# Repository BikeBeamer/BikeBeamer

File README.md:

# BikeBeamer

## Overview

This is my next generation of bike POV displays based on [bkpvdsply](https://github.com/locxter/bkpvdsply). With much extended functionality, a more polished design and an easier user-experience, the goal for it is to extend my capabilities and experiment with building a "real product" that lives up to the expectations one might have. Also take a look at the [project website](https://bikebeamer.com) or the launch video:

## Dependencies

I generally try to minimize dependencies, but I'm a one man crew and can therefore only support Debian-based Linux distributions as I'm running one myself. Anyway, you need to have the following packages installed for everything to work properly:

- Arduino IDE as a way to compile the Arduino code. Install it with `sudo apt install arduino`.
- MPU6050_tockn library for communicating with the gyroscope. Install it via the integrated library manager.
- Adafruit NeoPixel library for controlling the LEDs. Install it via the integrated library manager.

Note there is an [issue with the ESP32 core library >=3.x and the NeoPixel library when using more than 75 pixels](https://github.com/adafruit/Adafruit_NeoPixel/issues/402). There is a [forked library with a fix](https://github.com/teknynja/Adafruit_NeoPixel/tree/esp32_rmt_memory_allocation_fix_safe).

There some slight differences, depending on which major version of the Arduino IDE you are using. Extensions are not compatible with both versions. An extension is needed for uploading the data to the ESP32 LittleFS.

### Arduino IDE 1.x

Use the Arduino ESP32 LittleFS uploader for uploading the data. Install it via the [installation guide](https://github.com/lorol/arduino-esp32fs-plugin).

### Arduino IDE 2.x

Use the [Arduino LittleFS upload extension](https://github.com/earlephilhower/arduino-littlefs-upload).

## Improvements over bkpvdsply

### Hardware

- [x] Reduce the overall height to fit slimmer wheels
- [x] Rethink the mounting system to be easier for the user
- [x] FAILED: ~~Switch to a reusable cable tie alternative~~
- [x] Improve the water resistance (ideally water proof)
- [x] Make everything more balanced (equal weight distribution)
- [x] Add LED strips to both sides

### Electronics

- [x] Improve battery runtime
- [x] ABANDONED VIA SWITCH TO BATTERIES: ~~Make charging easier~~
- [x] Develop a properly sized power supply unit
- [x] Use custom-made circuit boards
- [ ] Switch to all SMT components
- [ ] Off-hand to production to a specialized vendor

### Software

- [x] Implement customizable LED strip positions (relative to control board)
- [x] Allow the rotation direction to be reversed (when the control board back faces right)
- [x] Use LED trips on both sides to display the image
- [x] Allow the image to be mirrored for the second side (useful for symbols and graphics, but not text)
- [ ] Reduce storage size of images (ideally via file compression)
- [ ] Add the ability to make animations with more than 2 images
- [x] Improve image stability (more exact rotation and speed change detection, smooth measuremets)
- [x] Implement customizable sampling threshold (allowed variation to trigger rotation detection)
- [X] Rework API with clearer endpoints
- [x] Load existing settings to UI for easier incremental changes
- [x] Store and load associative names of images for easier identification

And more to come...

## How to build it

In order to create a device able to produce such wonderful visuals, you only need rather common components (an ESP32, some LED strips, an IMU and some sort of power supply), but their combination results in this really special outcome. Everything is based on a custom PCB onto which all of the other components are soldered and which is then encased in 3D printed parts. Here's what the finished outcome should look like:

Even though many sequences of assembly will result in functional boards, here's how I assemble them after trying out several approaches with varying success:

1. In case you went for the cheap battery holders from Amazon, cut off the brim on the bottom, sand this side for better adhesive contact, shorten the wires and tin them in advance.
2. As always, parts should be soldered in the order of their height. So start off with cutting the LED strips to their desired length of 32 LEDs and then solder them down with the arrows facing towards the slim end of the boards from each side. It's easiest to solder one side of a strip, apply some instant glue along it's way and then solder the other one mounting it into place.
3. After that's done, continue with the diodes - be careful to install them the right way around (silver ring facing the marked direction) - and On/Off switch.
4. Now it's time install the ESP32 and IMU. Solder male headers facing down to the D1 Mini board in case not already done and then mount their female counterparts to the main PCB. You can also fill the contacts on the other boards, but that's not necessary. Then add the right-angle connector to the MPU-6050 board so that it can be mounted vertically to the PCB with its back facing to the wide end of the board and solder it down.
5. You're getting there, just add the screw terminals and then capacitors with the polarity of the latter being crucial (white component markings should face the filled side on the PCB).
6. If necessary glue down the battery holders and then solder them into place - this can be quite tight, but should be doable.
7. To prevent shorts with the spokes from happing isolate the back side with some duck tape or equivalent material. If you want everything to be more moisture resistant, you can also look into spray rubber products.
8. Finally, install the connection cables in the consistent matter and make sure that there are no shorts or other critical mistakes.
9. Once the electronics are done, cut the Plexiglas sheet into 8 14x222mm big pieces, glue them into the 3D prints (4 bottom + 4 top parts) and put them together (bottom part + PCB + top part, 4 times).

Below is a full bill of materials with German sources for all required non-printable parts:

| Quantity (not necessarily the order quantity): | Item: | Source: |
| --- | --- | --- |
| 1 | ESP32 D1 Mini | [Amazon](https://www.amazon.de/dp/B08BTLYSTM) |
| 1 | MPU-6050 | [Amazon](https://www.amazon.de/AZDelivery-MPU-6050-3-Achsen-Gyroskop-Beschleunigungssensor-Arduino/dp/B07TKLYBD6) |
| 2 | LED strip (144 LEDs/m) | [Amazon](https://www.amazon.de/dp/B08JJ6S1HC) |
| 12 | Battery holder | [RS Components](https://de.rs-online.com/web/p/batteriehalter/6119576) OR [Amazon](https://www.amazon.de/AA-Batteriehalter-KUOQIY-Batteriehalter-Drahtkabeln-Schraubendreher/dp/B0C2Q6JV88) |
| 4 | Power switch | [RS Components](https://de.rs-online.com/web/p/schiebeschalter/7347334) OR [Amazon](https://www.amazon.de/RUNCCI-YUN-Schiebeschalter-Positionen-Vertikal-Schalter/dp/B09TVDZ8P2) |
| 12 | Power smoothing capacitor (1000μF) | [RS Components](https://de.rs-online.com/web/p/aluminium-elektrolytkondensatoren/1815420) OR [Amazon](https://www.amazon.de/Kondensator-radial-1000%C2%B5F-RJF-10V102MH4-1000uF/dp/B07H9BFK31) |
| 4 | Reverse-voltage diode (1N5820) | [RS Components](https://de.rs-online.com/web/p/schottky-dioden-und-gleichrichter/6547224) OR [Amazon](https://www.amazon.de/ALLECIN-1N5820-Schottky-Gleichrichterdiode-Siliziumdioden/dp/B0CKSH71TP) |
| 6 | Screw terminal | [RS Components](https://de.rs-online.com/web/p/leiterplatten-printklemmen/1731613) OR [Amazon](https://www.amazon.de/RUNCCI-St%C3%BCcke-Terminal-Schraubklemme-Steckverbinder/dp/B07RR7D267) |
| 6 | JST SM 3 pin cable | [Amazon](https://www.amazon.de/YIXISI-M%C3%A4nnlichen-Weiblichen-Steckverbinder-Elektrisch/dp/B08JV8TJ9N) |
| 12 | AA battery | [Amazon](https://www.amazon.de/Varta-Industrial-Batterie-Alkaline-Batterien-blau/dp/B00LN803LE) |
| 15 | Cable ties | [Amazon](https://www.amazon.de/Kabelbinder-Rscolila-Hochleistungs-Kabelmanagement-300mmx5mm/dp/B09MVKD5YX) |
| 1 | Duck tape | [Amazon](https://www.amazon.de/3M-Gewebeklebeband-1900-Schwarz-1-er/dp/B006MKBVNM) |
| 3 | Instant glue | [Amazon](https://www.amazon.de/Uhu-45415-Sekundenkleber-Blitzschnell-fl%C3%BCssig/dp/B001IVZMBM) |
| 1 | Plexiglas sheet | [Amazon](https://www.amazon.de/Langaelex-transparentes-Plexiglasscheibe-Ersatzglas-Projektausstellung/dp/B0CL93YGQ2) |
| 18 | Wire ferrules | [Amazon](https://www.amazon.de/BAURIX-Aderendh%C3%BClsen-Sortiment-Isolierte-sortiert/dp/B07R6N5MGC) |

## How to use it

1. Build the hardware as described above and put the batteries in.
2. Select the "WEMOS D1 MINI ESP32" board in the Arduino IDE.
3. Flash the sketch with the following settings:
    - `Upload Speed: 9215600`
    - `CPU Frequency: 240MHz (WiFi/BT)`
    - `Flash Frequency: 80MHz`
    - `Partition Scheme: No OTA (Large APP)`
    - `Core Debug Level: None`
    - `Erase All Flash Before Sketch Upload: Disabled`
4. Upload the additional files via the Arduino ESP32 LittleFS uploader.
5. After turning on BikeBeamer, give the ESP roughly half a minute to boot up.
6. Connect to the Wi-Fi network `BikeBeamer`, open any webpage (or `192.168.0.1` if the local DNS server doesn't work) and upload an image (examples are in the `images` folder).
7. Test the assembled hardware on your workbench and check if everything works as expected. Here is some reference footage:

    [Loose boards in action](loose-in-action.mp4)

    https://github.com/user-attachments/assets/22288a13-f305-4ee8-a11e-b3bcc51daa01

8. Mount it on your bike with some cable ties like this:

9. Then just hop on your bike and enjoy the glory of this next generation POV display. Here's just some inspiration:

    [Mounted boards in action](mounted-in-action.mp4)

    https://github.com/user-attachments/assets/4a3be52c-16f3-4a09-bf7f-77527c5345b7

## Developer notes

- All angles used are in counted in degrees clockwise from 12 o'clock looking at the left side of the bike
- All coordinate systems used have their origin at the bottom left
- The PCBs are mounted with the back side visible when looking at the left side of the bike and connected in clockwise direction
- All indexes in the code are zero-based, while all user interfaces and visualisations use regular one-based numbering
- All API communication is done through HTTP headers for the sake of easy parsing in the front- and backend

### Mounting visualisation

### Image display visualisation

### API

- [x] User interface: GET /index.html

#### Settings

- [x] Get stored settings: GET /api/settings
- [X] Update settings: PUT /api/settings

#### Images

- [x] Get image names: GET /api/images
- [X] Update image: PUT /api/images/{slot}

## Similiar projects

- https://subethasoftware.com/bikelights/
- https://www.kickstarter.com/projects/minimonkey/monkey-light-pro-bicycle-wheel-display-system/description
- https://learn.adafruit.com/spokepov/overview
- https://www.ladyada.net/make/spokepov/
- https://learn.adafruit.com/bike-wheel-pov-display/overview
- https://bicycletouringpro.com/hokey-spokes-bicycle-lights-review/

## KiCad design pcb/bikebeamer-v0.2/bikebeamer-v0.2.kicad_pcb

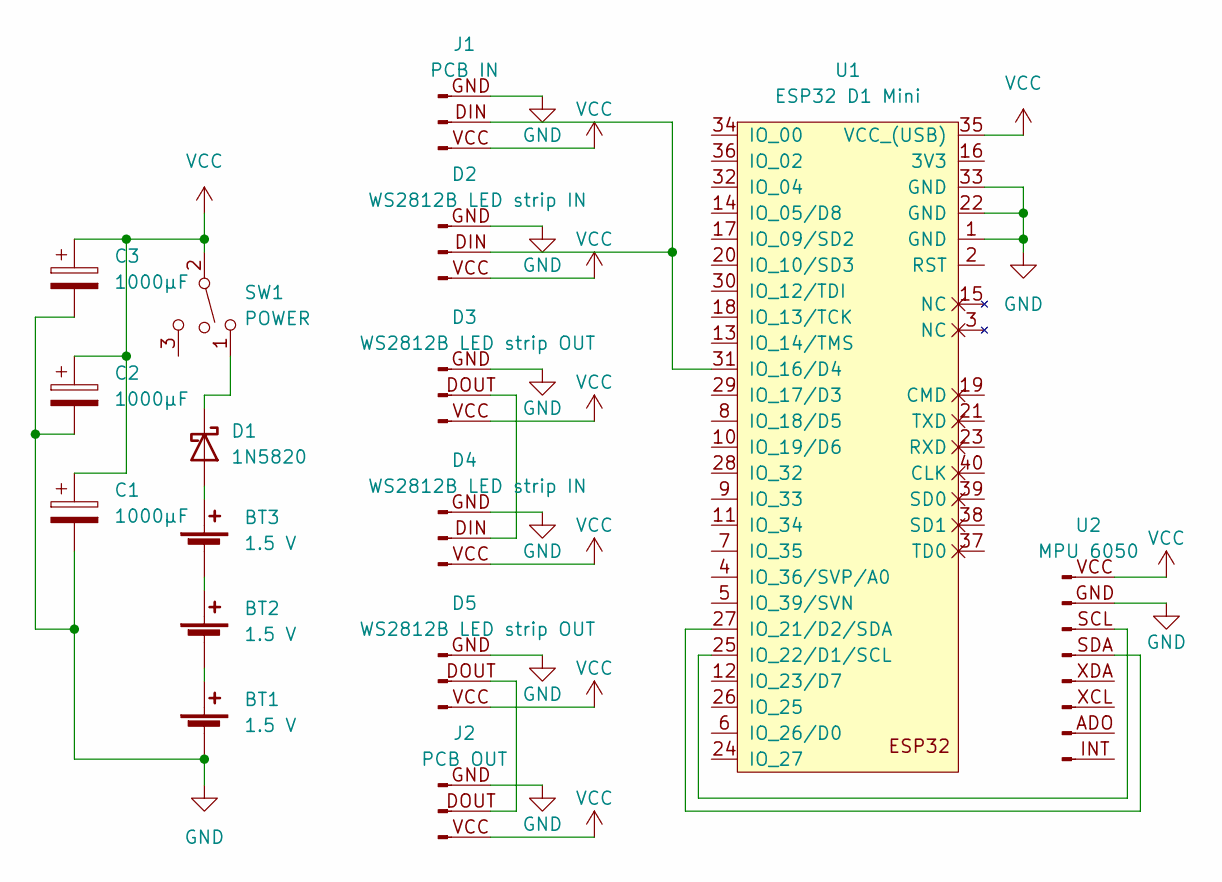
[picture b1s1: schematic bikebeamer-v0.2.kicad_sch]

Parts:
BT1, BT2, BT3: 1.5 V; BatteryHolder_Keystone_2460_1xAA
C1, C2, C3: 1000µF; CP_Radial_D10.0mm_P5.00mm
D1: 1N5820; D_DO-201AD_P15.24mm_Horizontal
D2, D4: WS2812B LED strip IN; PhoenixContact_MCV_1,5_3-G-5.08_1x03_P5.08mm_Vertical
D3, D5: WS2812B LED strip OUT; PhoenixContact_MCV_1,5_3-G-5.08_1x03_P5.08mm_Vertical
J1: PCB IN; PhoenixContact_MCV_1,5_3-G-5.08_1x03_P5.08mm_Vertical
J2: PCB OUT; PhoenixContact_MCV_1,5_3-G-5.08_1x03_P5.08mm_Vertical
SW1: POWER; SW_Slide_1P2T_CK_OS102011MS2Q
U1: ESP32 D1 Mini; ESP32_mini
U2: MPU 6050; PinHeader_1x08_P2.54mm_Vertical

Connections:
GND: BT1.2 (-), C1.2, C2.2, C3.2, D2.GND (Pin_1), D3.GND (Pin_1), D4.GND (Pin_1), D5.GND (Pin_1), J1.GND (Pin_1), J2.GND (Pin_1), U1.1 (GND), U1.22 (GND), U1.33 (GND), U2.GND (Pin_2)
unnamed: BT1.1 (+), BT2.2 (-)
unnamed: BT2.1 (+), BT3.2 (-)
unnamed: BT3.1 (+), D1.2 (A)
unnamed: D1.1 (K), SW1.1
unnamed: D2.DIN (Pin_2), J1.DIN (Pin_2), U1.31 (IO_16/D4)
unnamed: D3.DOUT (Pin_2), D4.DIN (Pin_2)
unnamed: D5.DOUT (Pin_2), J2.DOUT (Pin_2)
unnamed: U1.25 (IO_22/D1/SCL), U2.SCL (Pin_3)
unnamed: U1.27 (IO_21/D2/SDA), U2.SDA (Pin_4)
VCC: C1.1, C2.1, C3.1, D2.VCC (Pin_3), D3.VCC (Pin_3), D4.VCC (Pin_3), D5.VCC (Pin_3), J1.VCC (Pin_3), J2.VCC (Pin_3), SW1.2, U1.35 (VCC_(USB)), U2.VCC (Pin_1)

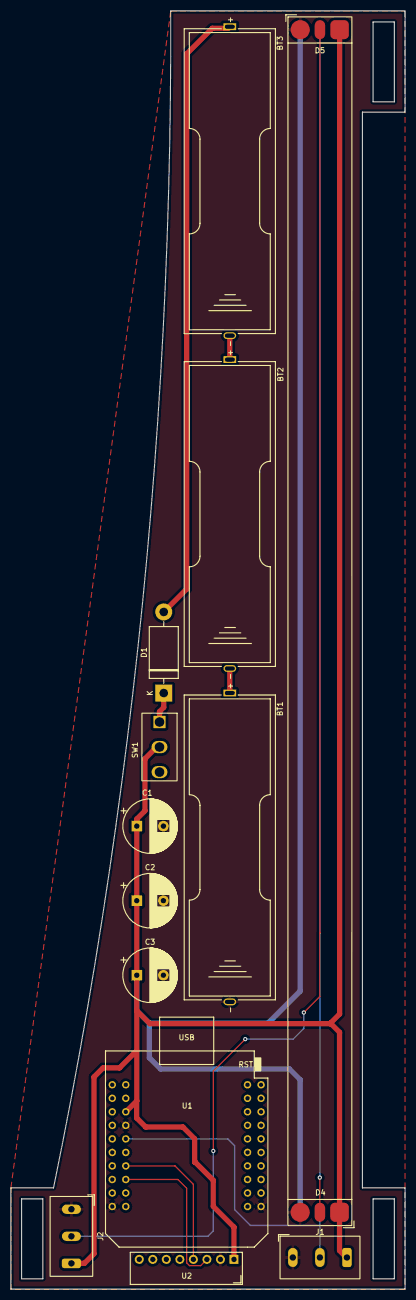
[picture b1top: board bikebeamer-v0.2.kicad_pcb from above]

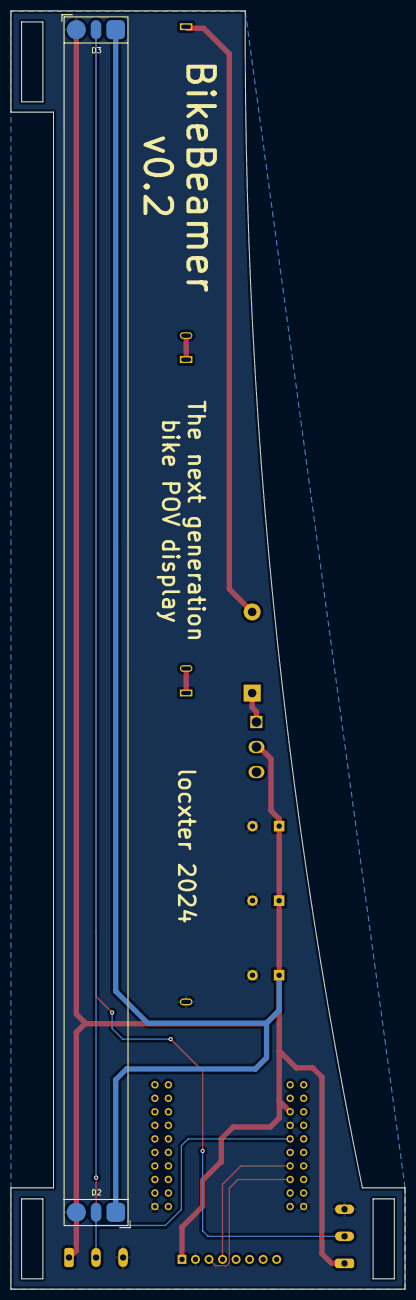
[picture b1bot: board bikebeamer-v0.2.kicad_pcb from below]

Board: 2 copper layers, 74.0 x 240.0 mm, 16 parts (2 on the bottom side), 11 nets.

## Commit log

2023-12-11 Uploaded already existing files.
2023-12-11 Updated license.
2023-12-12 Wrote a proper README.
2023-12-13 Removed all mentions of bkpvdsply in the code.
2023-12-13 Implemented customizable LED strip position.
2023-12-13 Implemented reverse rotation direction.
2023-12-13 Fixed a typo.
2023-12-13 Fixed a image upload bug with transparent backgrounds.
2023-12-13 Added a test image by default and made sure settings changes are immediately applied.
2023-12-15 Added some references and development visualisations to README.
2023-12-15 Implemented the first experimental support for LEDs on both side. Still needs to be tested.
2023-12-15 Removed some unnecessary global variables from frontend.
2023-12-15 Small frontend performance improvement.
2023-12-16 Reworked the READE somewhat.
2023-12-16 Implemented customizable sampling threshold.
2023-12-16 Implemented experimental image stability improvements.
2023-12-17 Fixed a small logical error regarding the actual counterclockwise rotation of the wheel and the internal clockwise angle calculation.
2023-12-17 Renamed virtualAngleOffset to revolutionOffset to better reflect its function.
2023-12-17 Fixed the rotation detection and tweaked default settings.
2023-12-17 Implemented sample smoothing and successfully tested the existing functionality.
2023-12-28 Reworked the README with an overview image and some MonkeyLight inspirations, added two sample images and created a storage backup of the prototype.
2024-01-02 Designed a first prototype PCB and updated the README.
2024-01-02 Updated the mounting visualisation and code to accomodate the new PCB.
2024-01-02 Updated the license to 2024.
2024-01-03 Forgot to updated the config website as well.
2024-01-03 Tweaked the mounting visualisation to reflect the new control board and battery pack locations.
2024-01-04 Added a note clarifying the indexing to README and removed storage backup.
2024-01-04 Removed the strip 0 position and reverse direction option, since both become obsolete with the new PCB.
2024-01-13 Added a boot confirmation blink and updated the settings UI to mattch the default values used.
2024-01-13 Updated the progress in the README.
2024-01-13 Removed the outdated CAD files and added some build instructions to the README.
2024-01-13 Changed the work in progress message.
2024-01-15 Designed a first prototype case.
2024-01-16 Fixed some minor design flaws I noticed after printing.
2024-01-16 Added the case to the documentation.
2024-01-16 Implemented easier to tweak revolution period averaging.
2024-01-17 Fxied a missing feature due to invalid dependencies.
2024-01-18 Fixed another CAD dependency issue.
2024-01-20 Added a picture of the encased boards.
2024-01-20 Fixed some small mistakes and uncertain wordings in the README.
2024-01-24 Moved the LED strip pads 1mm further apart.
2024-01-24 Updated the case with grooves for rubber bands to keep the top in place.
2024-01-27 Fixed animation dropouts at high speeds.
2024-01-27 Added some pictures of the encased boards being mounted.
2024-01-28 Implemented user-changable revolution period averaging.
2024-01-28 Updated default settings for higher image stability and brightness.
2024-01-28 Updated a frontend error message.
2024-01-28 Added some tweaks to the revolution period averaging to make sure that it gets reset on cycling pauses and only takes non-zero measurements into account when beginning to drive again.
2024-02-17 Slightly increased case top tolerances.
2024-02-23 Added new software goals to README.
2024-02-24 Implemented associative names for images and loading settings to UI.
2024-02-24 Finished reworking the API.
2024-02-24 Forgot two semi-important comments ;)
2024-02-25 Minor README improvements.
2024-03-01 Removed my username from the UI footer.
2024-04-27 Reworked the overview image.
2024-06-05 Fixed a typo in the README.
2024-06-11 Prepared the README for public release.
2024-08-31 Embedded videos into README.
2024-08-31 Another attempt at embedding videos into README.
2024-08-31 Finally got the videos to show up in README
2024-08-31 Compressed a video to fit within the 10 mb file limit of GitHub embeds.
2024-08-31 Fixed bullet point numbering in README.
2024-09-21 Added the launch video to the README.
2024-09-21 Fixed the YouTube video emned.
2024-12-15 docs: dependencies for Arduino IDE 2.x and latest ESP32 core libs
